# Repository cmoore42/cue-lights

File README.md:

# Theatrical Cue Light system

This project contains hardware and firmware designs to build a multi-station cue light system.

Please see the Wiki pages for more information and documentation.

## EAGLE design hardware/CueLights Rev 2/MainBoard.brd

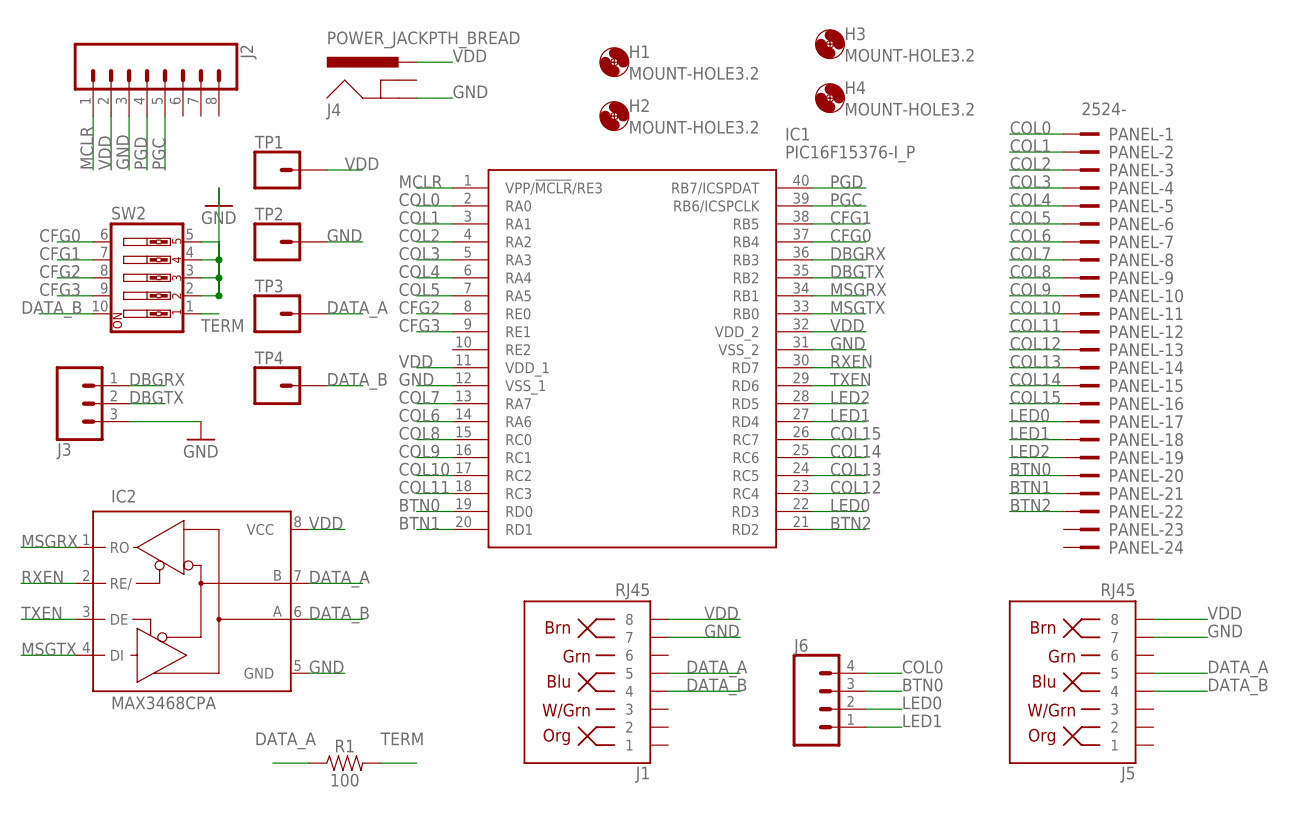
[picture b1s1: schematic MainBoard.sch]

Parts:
H1, H2, H3, H4: MOUNT-HOLE3.2; 3,2
IC1: PIC16F15376-I_P; DIP1550W56P254L5219H483Q40N
IC2: MAX3468CPA; DIL08
J1, J5: RJ45; RJ45-8
J2: CONN_08"; 1X08
J3: CONN_03; 1X03
J4: POWER_JACKPTH_BREAD; POWER_JACK_PTH_BREAD
J6: CONN_04; 1X04
PANEL: 2524-; PAK100/2500-24
R1: 100; AXIAL-0.3
SW2: SW_DIP-5; EDG-05
TP1, TP2, TP3, TP4: CONN_01; 1X01

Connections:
BTN0: IC1.19 (RD0), J6.3, PANEL.20
BTN1: IC1.20 (RD1), PANEL.21
BTN2: IC1.21 (RD2), PANEL.22
CFG0: IC1.37 (RB4), SW2.6
CFG1: IC1.38 (RB5), SW2.7
CFG2: IC1.8 (RE0), SW2.8
CFG3: IC1.9 (RE1), SW2.9
COL0: IC1.2 (RA0), J6.4, PANEL.1
COL1: IC1.3 (RA1), PANEL.2
COL2: IC1.4 (RA2), PANEL.3
COL3: IC1.5 (RA3), PANEL.4
COL4: IC1.6 (RA4), PANEL.5
COL5: IC1.7 (RA5), PANEL.6
COL6: IC1.14 (RA6), PANEL.7
COL7: IC1.13 (RA7), PANEL.8
COL8: IC1.15 (RC0), PANEL.9
COL9: IC1.16 (RC1), PANEL.10
COL10: IC1.17 (RC2), PANEL.11
COL11: IC1.18 (RC3), PANEL.12
COL12: IC1.23 (RC4), PANEL.13
COL13: IC1.24 (RC5), PANEL.14
COL14: IC1.25 (RC6), PANEL.15
COL15: IC1.26 (RC7), PANEL.16
DATA_A: IC2.7 (B), J1.5, J5.5, R1.P$1 (1), TP3.1
DATA_B: IC2.6 (A), J1.4, J5.4, SW2.10, TP4.1
DBGRX: IC1.36 (RB3), J3.1
DBGTX: IC1.35 (RB2), J3.2
GND: IC1.12 (VSS_1), IC1.31 (VSS_2), IC2.5 (GND), J1.7, J2.3, J3.3, J4.GND, J5.7, SW2.2, SW2.3, SW2.4, SW2.5, TP2.1
LED0: IC1.22 (RD3), J6.2, PANEL.17
LED1: IC1.27 (RD4), J6.1, PANEL.18
LED2: IC1.28 (RD5), PANEL.19
MCLR: IC1.1 (VPP/!MCLR!/RE3), J2.1
MSGRX: IC1.34 (RB1), IC2.1 (RO)
MSGTX: IC1.33 (RB0), IC2.4 (DI)
PGC: IC1.39 (RB6/ICSPCLK), J2.5
PGD: IC1.40 (RB7/ICSPDAT), J2.4
RXEN: IC1.30 (RD7), IC2.2 (RE/)
TERM: R1.P$2 (2), SW2.1
TXEN: IC1.29 (RD6), IC2.3 (DE)
VDD: IC1.11 (VDD_1), IC1.32 (VDD_2), IC2.8 (VCC), J1.8, J2.2, J4.PWR, J5.8, TP1.1

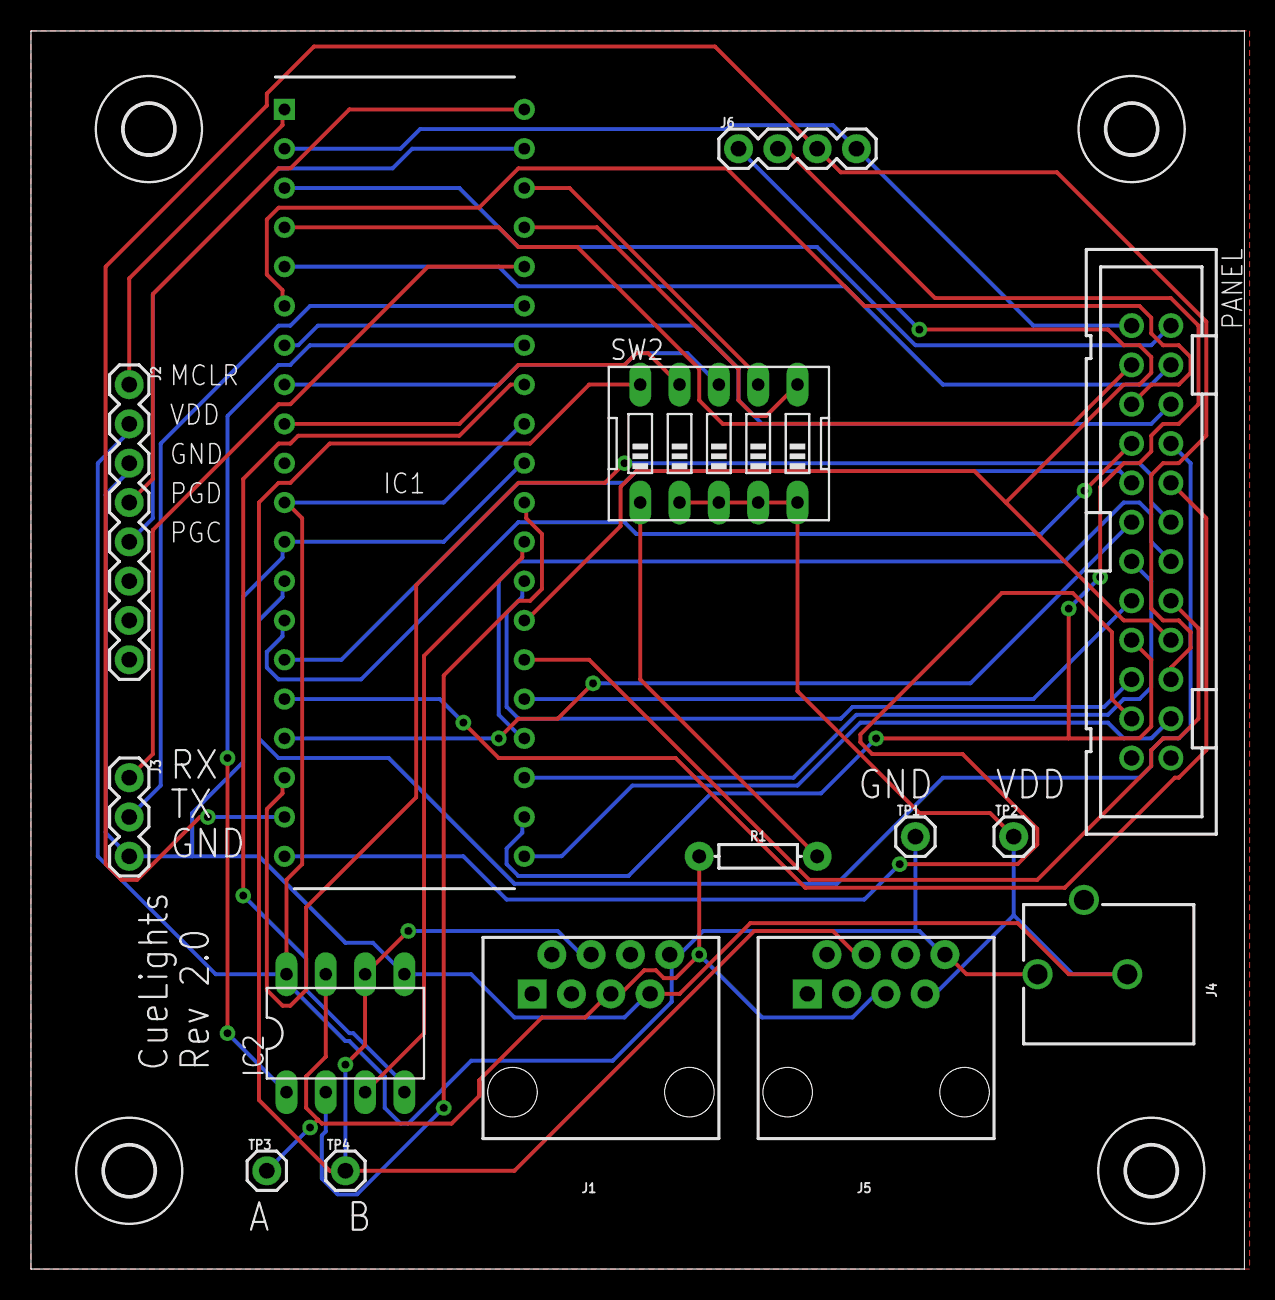
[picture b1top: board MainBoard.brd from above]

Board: 2 copper layers, 78.4 x 80.0 mm, 19 parts (0 on the bottom side), 40 nets.

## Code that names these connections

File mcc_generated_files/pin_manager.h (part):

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// get/set COL0 aliases
#define COL0_TRIS                 TRISAbits.TRISA0
#define COL0_LAT                  LATAbits.LATA0
#define COL0_PORT                 PORTAbits.RA0
#define COL0_WPU                  WPUAbits.WPUA0
#define COL0_OD                   ODCONAbits.ODCA0
#define COL0_ANS                  ANSELAbits.ANSA0
#define COL0_SetHigh()            do { LATAbits.LATA0 = 1; } while(0)
#define COL0_SetLow()             do { LATAbits.LATA0 = 0; } while(0)
#define COL0_Toggle()             do { LATAbits.LATA0 = ~LATAbits.LATA0; } while(0)
#define COL0_GetValue()           PORTAbits.RA0
#define COL0_SetDigitalInput()    do { TRISAbits.TRISA0 = 1; } while(0)
#define COL0_SetDigitalOutput()   do { TRISAbits.TRISA0 = 0; } while(0)
#define COL0_SetPullup()          do { WPUAbits.WPUA0 = 1; } while(0)
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// get/set COL1 aliases
#define COL1_TRIS                 TRISAbits.TRISA1
#define COL1_LAT                  LATAbits.LATA1
#define COL1_PORT                 PORTAbits.RA1
#define COL1_WPU                  WPUAbits.WPUA1
#define COL1_OD                   ODCONAbits.ODCA1
#define COL1_ANS                  ANSELAbits.ANSA1
#define COL1_SetHigh()            do { LATAbits.LATA1 = 1; } while(0)
#define COL1_SetLow()             do { LATAbits.LATA1 = 0; } while(0)
#define COL1_Toggle()             do { LATAbits.LATA1 = ~LATAbits.LATA1; } while(0)
#define COL1_GetValue()           PORTAbits.RA1
#define COL1_SetDigitalInput()    do { TRISAbits.TRISA1 = 1; } while(0)
#define COL1_SetDigitalOutput()   do { TRISAbits.TRISA1 = 0; } while(0)
#define COL1_SetPullup()          do { WPUAbits.WPUA1 = 1; } while(0)
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// get/set COL2 aliases
#define COL2_TRIS                 TRISAbits.TRISA2
#define COL2_LAT                  LATAbits.LATA2
#define COL2_PORT                 PORTAbits.RA2
#define COL2_WPU                  WPUAbits.WPUA2
#define COL2_OD                   ODCONAbits.ODCA2
#define COL2_ANS                  ANSELAbits.ANSA2
#define COL2_SetHigh()            do { LATAbits.LATA2 = 1; } while(0)
#define COL2_SetLow()             do { LATAbits.LATA2 = 0; } while(0)
#define COL2_Toggle()             do { LATAbits.LATA2 = ~LATAbits.LATA2; } while(0)
#define COL2_GetValue()           PORTAbits.RA2
#define COL2_SetDigitalInput()    do { TRISAbits.TRISA2 = 1; } while(0)
#define COL2_SetDigitalOutput()   do { TRISAbits.TRISA2 = 0; } while(0)
#define COL2_SetPullup()          do { WPUAbits.WPUA2 = 1; } while(0)
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// get/set COL3 aliases
#define COL3_TRIS                 TRISAbits.TRISA3
#define COL3_LAT                  LATAbits.LATA3
#define COL3_PORT                 PORTAbits.RA3
#define COL3_WPU                  WPUAbits.WPUA3
#define COL3_OD                   ODCONAbits.ODCA3
#define COL3_ANS                  ANSELAbits.ANSA3
#define COL3_SetHigh()            do { LATAbits.LATA3 = 1; } while(0)
#define COL3_SetLow()             do { LATAbits.LATA3 = 0; } while(0)
#define COL3_Toggle()             do { LATAbits.LATA3 = ~LATAbits.LATA3; } while(0)
#define COL3_GetValue()           PORTAbits.RA3
#define COL3_SetDigitalInput()    do { TRISAbits.TRISA3 = 1; } while(0)
#define COL3_SetDigitalOutput()   do { TRISAbits.TRISA3 = 0; } while(0)
#define COL3_SetPullup()          do { WPUAbits.WPUA3 = 1; } while(0)
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// get/set COL4 aliases
#define COL4_TRIS                 TRISAbits.TRISA4
#define COL4_LAT                  LATAbits.LATA4
#define COL4_PORT                 PORTAbits.RA4
#define COL4_WPU                  WPUAbits.WPUA4
#define COL4_OD                   ODCONAbits.ODCA4
#define COL4_ANS                  ANSELAbits.ANSA4
#define COL4_SetHigh()            do { LATAbits.LATA4 = 1; } while(0)
#define COL4_SetLow()             do { LATAbits.LATA4 = 0; } while(0)
#define COL4_Toggle()             do { LATAbits.LATA4 = ~LATAbits.LATA4; } while(0)
#define COL4_GetValue()           PORTAbits.RA4
#define COL4_SetDigitalInput()    do { TRISAbits.TRISA4 = 1; } while(0)
#define COL4_SetDigitalOutput()   do { TRISAbits.TRISA4 = 0; } while(0)
#define COL4_SetPullup()          do { WPUAbits.WPUA4 = 1; } while(0)
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// get/set COL5 aliases
#define COL5_TRIS                 TRISAbits.TRISA5
#define COL5_LAT                  LATAbits.LATA5
#define COL5_PORT                 PORTAbits.RA5
#define COL5_WPU                  WPUAbits.WPUA5
#define COL5_OD                   ODCONAbits.ODCA5
#define COL5_ANS                  ANSELAbits.ANSA5
#define COL5_SetHigh()            do { LATAbits.LATA5 = 1; } while(0)
#define COL5_SetLow()             do { LATAbits.LATA5 = 0; } while(0)
#define COL5_Toggle()             do { LATAbits.LATA5 = ~LATAbits.LATA5; } while(0)
#define COL5_GetValue()           PORTAbits.RA5
#define COL5_SetDigitalInput()    do { TRISAbits.TRISA5 = 1; } while(0)
#define COL5_SetDigitalOutput()   do { TRISAbits.TRISA5 = 0; } while(0)
#define COL5_SetPullup()          do { WPUAbits.WPUA5 = 1; } while(0)
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// get/set COL6 aliases
#define COL6_TRIS                 TRISAbits.TRISA6
#define COL6_LAT                  LATAbits.LATA6
#define COL6_PORT                 PORTAbits.RA6
#define COL6_WPU                  WPUAbits.WPUA6
#define COL6_OD                   ODCONAbits.ODCA6
#define COL6_ANS                  ANSELAbits.ANSA6
#define COL6_SetHigh()            do { LATAbits.LATA6 = 1; } while(0)
#define COL6_SetLow()             do { LATAbits.LATA6 = 0; } while(0)
#define COL6_Toggle()             do { LATAbits.LATA6 = ~LATAbits.LATA6; } while(0)
#define COL6_GetValue()           PORTAbits.RA6
#define COL6_SetDigitalInput()    do { TRISAbits.TRISA6 = 1; } while(0)
#define COL6_SetDigitalOutput()   do { TRISAbits.TRISA6 = 0; } while(0)
#define COL6_SetPullup()          do { WPUAbits.WPUA6 = 1; } while(0)
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// get/set COL7 aliases
#define COL7_TRIS                 TRISAbits.TRISA7
#define COL7_LAT                  LATAbits.LATA7
#define COL7_PORT                 PORTAbits.RA7
#define COL7_WPU                  WPUAbits.WPUA7
#define COL7_OD                   ODCONAbits.ODCA7
#define COL7_ANS                  ANSELAbits.ANSA7
#define COL7_SetHigh()            do { LATAbits.LATA7 = 1; } while(0)
#define COL7_SetLow()             do { LATAbits.LATA7 = 0; } while(0)
#define COL7_Toggle()             do { LATAbits.LATA7 = ~LATAbits.LATA7; } while(0)
#define COL7_GetValue()           PORTAbits.RA7
#define COL7_SetDigitalInput()    do { TRISAbits.TRISA7 = 1; } while(0)
#define COL7_SetDigitalOutput()   do { TRISAbits.TRISA7 = 0; } while(0)
#define COL7_SetPullup()          do { WPUAbits.WPUA7 = 1; } while(0)
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#define RB0_SetHigh()            do { LATBbits.LATB0 = 1; } while(0)
#define RB0_SetLow()             do { LATBbits.LATB0 = 0; } while(0)
#define RB0_Toggle()             do { LATBbits.LATB0 = ~LATBbits.LATB0; } while(0)
#define RB0_GetValue()              PORTBbits.RB0
#define RB0_SetDigitalInput()    do { TRISBbits.TRISB0 = 1; } while(0)
#define RB0_SetDigitalOutput()   do { TRISBbits.TRISB0 = 0; } while(0)
#define RB0_SetPullup()             do { WPUBbits.WPUB0 = 1; } while(0)
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#define RB1_SetHigh()            do { LATBbits.LATB1 = 1; } while(0)
#define RB1_SetLow()             do { LATBbits.LATB1 = 0; } while(0)
#define RB1_Toggle()             do { LATBbits.LATB1 = ~LATBbits.LATB1; } while(0)
#define RB1_GetValue()              PORTBbits.RB1
#define RB1_SetDigitalInput()    do { TRISBbits.TRISB1 = 1; } while(0)
#define RB1_SetDigitalOutput()   do { TRISBbits.TRISB1 = 0; } while(0)
#define RB1_SetPullup()             do { WPUBbits.WPUB1 = 1; } while(0)
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#define RB2_SetHigh()            do { LATBbits.LATB2 = 1; } while(0)
#define RB2_SetLow()             do { LATBbits.LATB2 = 0; } while(0)
#define RB2_Toggle()             do { LATBbits.LATB2 = ~LATBbits.LATB2; } while(0)
#define RB2_GetValue()              PORTBbits.RB2
#define RB2_SetDigitalInput()    do { TRISBbits.TRISB2 = 1; } while(0)
#define RB2_SetDigitalOutput()   do { TRISBbits.TRISB2 = 0; } while(0)
#define RB2_SetPullup()             do { WPUBbits.WPUB2 = 1; } while(0)
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#define RB3_SetHigh()            do { LATBbits.LATB3 = 1; } while(0)
#define RB3_SetLow()             do { LATBbits.LATB3 = 0; } while(0)
#define RB3_Toggle()             do { LATBbits.LATB3 = ~LATBbits.LATB3; } while(0)
#define RB3_GetValue()              PORTBbits.RB3
#define RB3_SetDigitalInput()    do { TRISBbits.TRISB3 = 1; } while(0)
#define RB3_SetDigitalOutput()   do { TRISBbits.TRISB3 = 0; } while(0)
#define RB3_SetPullup()             do { WPUBbits.WPUB3 = 1; } while(0)
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// get/set CFG0 aliases
#define CFG0_TRIS                 TRISBbits.TRISB4
#define CFG0_LAT                  LATBbits.LATB4
#define CFG0_PORT                 PORTBbits.RB4
#define CFG0_WPU                  WPUBbits.WPUB4
#define CFG0_OD                   ODCONBbits.ODCB4
#define CFG0_ANS                  ANSELBbits.ANSB4
#define CFG0_SetHigh()            do { LATBbits.LATB4 = 1; } while(0)
#define CFG0_SetLow()             do { LATBbits.LATB4 = 0; } while(0)
#define CFG0_Toggle()             do { LATBbits.LATB4 = ~LATBbits.LATB4; } while(0)
#define CFG0_GetValue()           PORTBbits.RB4
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
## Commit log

2019-01-01 Changed EUSART1 baud rate to 250Kbps, to match DMX.
2019-01-05 Changed message type names to be more clear Modified the slave poll response to always send back its state
2019-01-05 Only call dbg print functions if DEBUG is defined.
2019-01-08 Slave button should only go to READY if already in STANDBY.
2019-04-12 Added the schematic and board layout.
2019-04-12 Added the 3D models

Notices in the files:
mcc_generated_files/pin_manager.h:
(c) 2018 Microchip Technology Inc. and its subsidiaries.
parts and their libraries:
SparkFun-Connectors: Licensing: Creative Commons ShareAlike 4.0 International - https://creativecommons.org/licenses/by-sa/4.0
